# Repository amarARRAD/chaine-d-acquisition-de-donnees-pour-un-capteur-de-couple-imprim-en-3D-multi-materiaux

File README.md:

# Chaîne d’acquisition pour capteur de couple capacitif imprimé en 3D (ESP32-S3 + FDC1004)

Ce dépôt regroupe le travail réalisé dans le cadre du Master 2 EEEA (Systèmes embarqués) en collaboration avec l’Inria.  
Le projet vise à rendre autonome la mesure de couple d’un capteur capacitif imprimé en 3D multi-matériaux, destiné à une intégration dans un exosquelette.

## Principe
Le capteur comporte 4 structures capacitives. Lorsqu’un couple est appliqué, la déformation mécanique provoque des variations de capacité. Ces 4 mesures sont combinées pour obtenir une grandeur différentielle, puis un angle et enfin un couple estimé.

## Architecture matérielle
- **FDC1004** : convertisseur capacité-numérique (4 canaux) avec **blindage actif** (/Blinddd) pour limiter les capacités parasites.
- **ESP32-S3-WROOM-1** : récupération des mesures via **I2C**, traitement embarqué et communication.
- **PCB circulaire 2 couches** conçu pour être monté directement sur le capteur (plan de masse + plan de blindage).
- Interfaces prévues : **UART** (programmation / debug) et **CAN** (prévu pour intégration future exosquelette).

## Logiciel embarqué
Le traitement initialement réalisé sous MATLAB a été traduit en **C++ (ESP-IDF)** sous forme de librairie :
- driver I2C FDC1004 (lecture des 4 capacités, conversion en pF)
- calcul de la capacité différentielle (`Ctot`)
- estimation d’angle et de couple (modèle statique avec hystérésis + terme dynamique)

## Contenu du dépôt
- Fichiers **KiCad** (schéma + routage + fabrication)
- Code **C++ / ESP-IDF** (librairie capteur + exemples)
- Rapport (LaTeX) et annexes (datasheets / documents)

## Perspectives
- réintégration d’une **Flash externe**
- ajout de **filtrage numérique**
- ajout de capteurs complémentaires (température, IMU) pour améliorer la robustesse en conditions réelles

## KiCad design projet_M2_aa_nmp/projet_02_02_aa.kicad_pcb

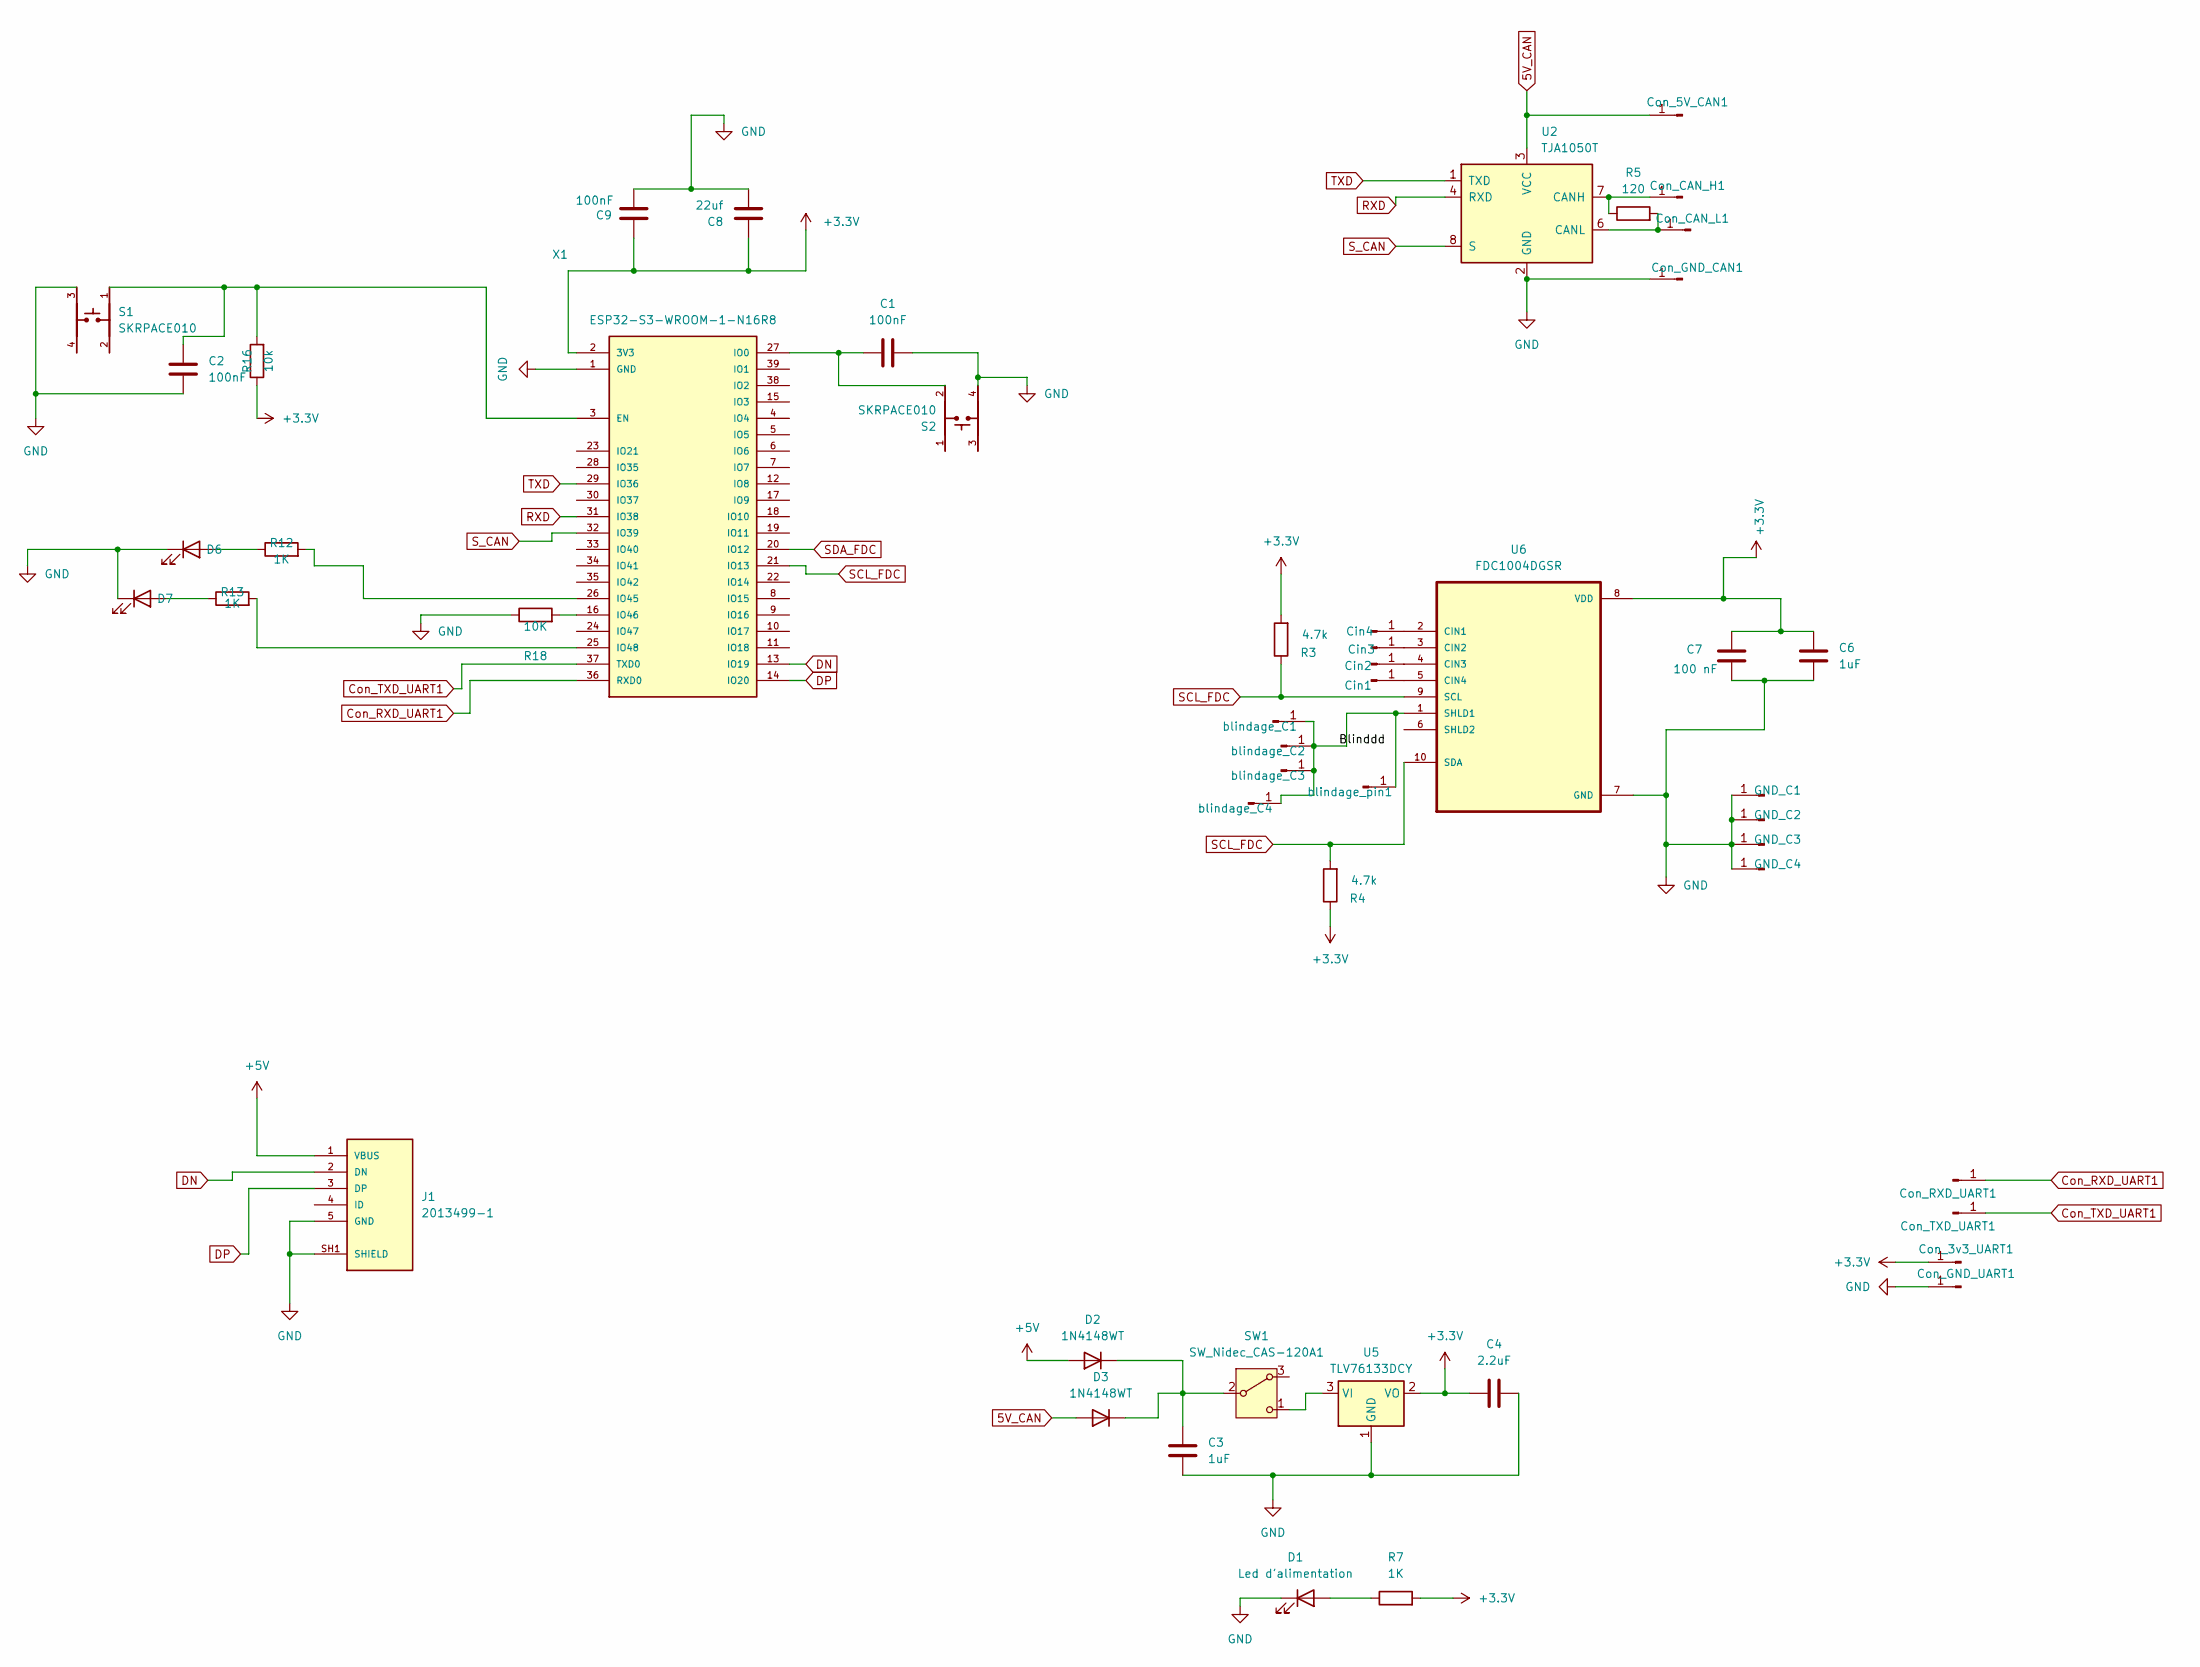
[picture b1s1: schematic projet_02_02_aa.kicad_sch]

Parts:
C1, C2, C9: 100nF; CP_Elec_3x5.3
C3, C6: 1uF; CP_Elec_3x5.3
C4: 2.2uF; CP_Elec_3x5.3
C7: 100 nF; CP_Elec_3x5.3
C8: 22uf; CP_Elec_3x5.3
Cin1, Cin2, Cin3, Cin4: Conn_01x01_Pin; PinHeader_1x01_P1.00mm_Vertical
Con_3v3_UART1, Con_5V_CAN1: Conn_01x01_Pin; PinHeader_1x01_P1.00mm_Vertical
Con_CAN_H1: Conn_01x01_Pin; PinHeader_1x01_P1.00mm_Vertical
Con_CAN_L1: Conn_01x01_Pin; PinHeader_1x01_P1.00mm_Vertical
Con_GND_CAN1: Conn_01x01_Pin; PinHeader_1x01_P1.00mm_Vertical
Con_GND_UART1: Conn_01x01_Pin; PinHeader_1x01_P1.00mm_Vertical
Con_RXD_UART1: Conn_01x01_Pin; PinHeader_1x01_P1.00mm_Vertical
Con_TXD_UART1: Conn_01x01_Pin; PinHeader_1x01_P1.00mm_Vertical
D1: Led d'alimentation; LED_1206_3216Metric
D2, D3: 1N4148WT; D_SOD-523
D6, D7: IR26-21C_L110_TR8; LED_1206_3216Metric
GND_C1, GND_C2, GND_C3, GND_C4: Conn_01x01_Pin; PinHeader_1x01_P1.00mm_Vertical
J1: 2013499-1; TE_2013499-1; PARTREV B5
R3, R4: 4.7k; R_0201_0603Metric
R5: 120; R_0201_0603Metric
R7, R12, R13: 1K; R_0201_0603Metric
R16: 10k; R_0201_0603Metric
R18: 10K; R_0201_0603Metric
S1, S2: SKRPACE010; SW_SKRPACE010
SW1: SW_Nidec_CAS-120A1; Nidec_Copal_CAS-120A
U2: TJA1050T; SOIC-8_3.9x4.9mm_P1.27mm
U5: TLV76133DCY; SOT-223-3_TabPin2
U6: FDC1004DGSR; MSOP-10-1EP_3x3mm_P0.5mm_EP1.73x1.98mm
X1: ESP32-S3-WROOM-1-N16R8; ESP32S3WROOM1N8R2; MANUFACTURER_PART_NUMBER ESP32-S3-WROOM-1-N16R8
blindage_C1, blindage_C2, blindage_C3, blindage_C4: Conn_01x01_Pin; PinHeader_1x01_P1.00mm_Vertical
blindage_pin1: Conn_01x01_Pin; PinHeader_1x01_P1.00mm_Vertical

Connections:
5V_CAN: Con_5V_CAN1.1, D3.2 (A), U2.3 (VCC)
+3.3V: C4.1, C6.2, C7.2, C8.2, C9.2, Con_3v3_UART1.1, R3.2, R4.1, R7.2, R16.1, U5.2 (VO), U6.8 (VDD), X1.2 (3V3)
+5V: D2.2 (A), J1.1 (VBUS)
/Blinddd: U6.1 (SHLD1), blindage_C1.1, blindage_C2.1, blindage_C3.1, blindage_C4.1, blindage_pin1.1
Con_RXD_UART1: Con_RXD_UART1.1, X1.36 (RXD0)
Con_TXD_UART1: Con_TXD_UART1.1, X1.37 (TXD0)
DN: J1.2 (DN), X1.13 (IO19)
DP: J1.3 (DP), X1.14 (IO20)
GND: C1.2, C2.1, C3.2, C4.2, C6.1, C7.1, C8.1, C9.1, Con_GND_CAN1.1, Con_GND_UART1.1, D1.1 (K), D6.1 (K), D7.1 (K), GND_C1.1, GND_C2.1, GND_C3.1, GND_C4.1, J1.5 (GND), J1.SH1 (SHIELD), J1.SH2 (SHIELD), J1.SH3 (SHIELD), J1.SH4 (SHIELD), J1.SH5 (SHIELD), J1.SH6 (SHIELD), R18.1, S1.3, S2.4, U2.2 (GND), U5.1 (GND), U6.7 (GND), X1.1 (GND), X1.40 (GND), X1.41 (GND), X1.42 (GND), X1.43 (GND), X1.44 (GND), X1.45 (GND), X1.46 (GND), X1.47 (GND), X1.48 (GND), X1.49 (GND)
unnamed: Cin1.1, U6.5 (CIN4)
unnamed: Cin2.1, U6.4 (CIN3)
unnamed: Cin3.1, U6.3 (CIN2)
unnamed: Cin4.1, U6.2 (CIN1)
unnamed: Con_CAN_H1.1, R5.1, U2.7 (CANH)
unnamed: Con_CAN_L1.1, R5.2, U2.6 (CANL)
unnamed: D1.2 (A), R7.1
unnamed: C3.1, D2.1 (K), D3.1 (K), SW1.2 (B)
unnamed: D6.2 (A), R12.1
unnamed: D7.2 (A), R13.1
unnamed: SW1.1 (C), U5.3 (VI)
unnamed: C2.2, R16.2, S1.1, X1.3 (EN)
unnamed: C1.1, S2.2, X1.27 (IO0)
unnamed: R12.2, X1.26 (IO45)
unnamed: R18.2, X1.16 (IO46)
unnamed: R13.2, X1.25 (IO48)
RXD: U2.4 (RXD), X1.31 (IO38)
S_CAN: U2.8 (S), X1.32 (IO39)
TXD: U2.1 (TXD), X1.29 (IO36)

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
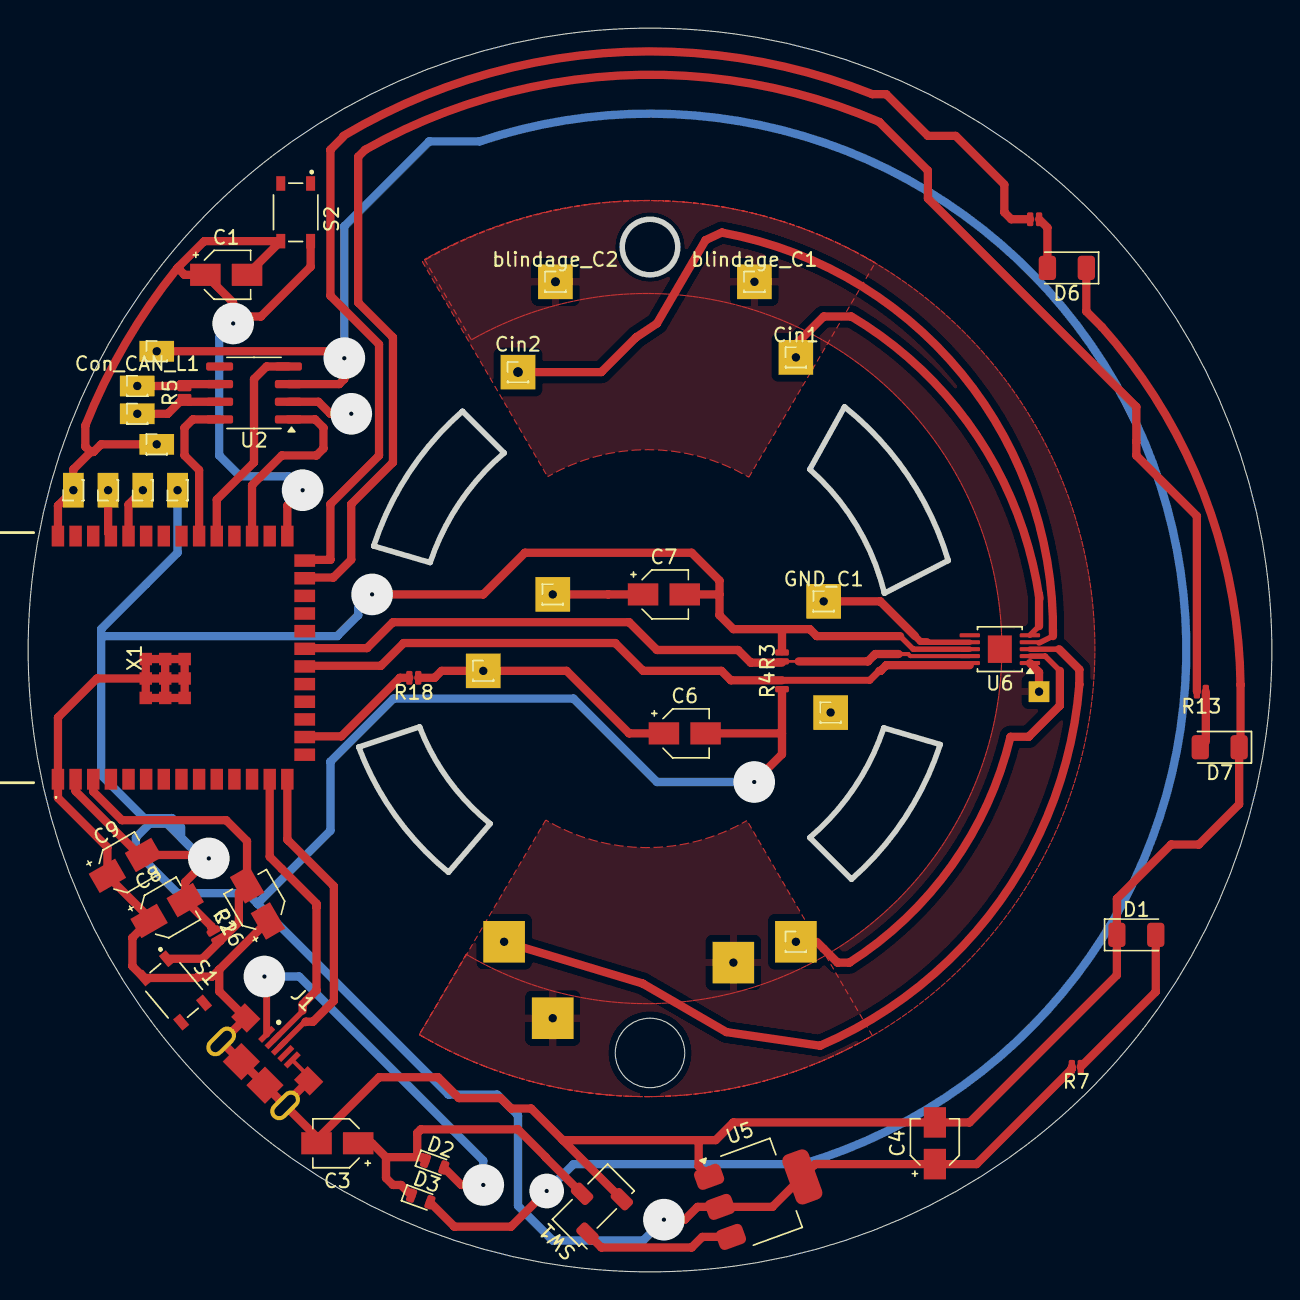
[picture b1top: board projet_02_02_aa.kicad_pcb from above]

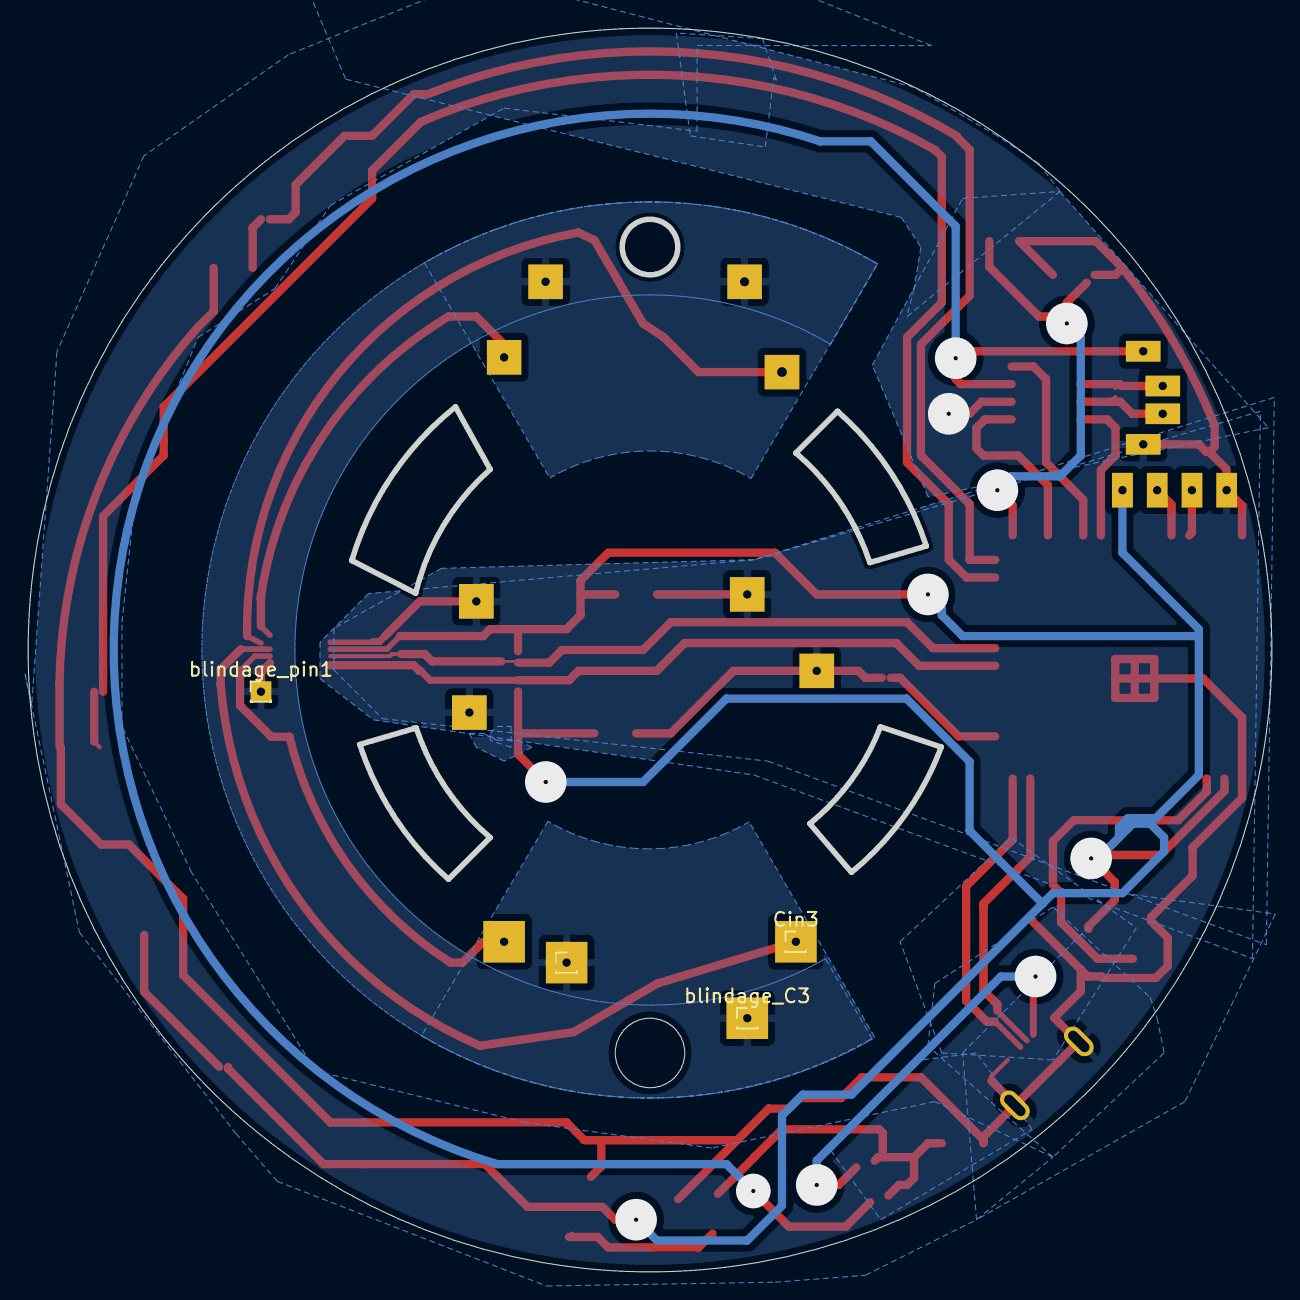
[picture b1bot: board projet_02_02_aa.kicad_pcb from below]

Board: 2 copper layers, 89.2 x 89.2 mm, 50 parts (4 on the bottom side), 30 nets.

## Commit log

2026-02-13 Ajout du projet
